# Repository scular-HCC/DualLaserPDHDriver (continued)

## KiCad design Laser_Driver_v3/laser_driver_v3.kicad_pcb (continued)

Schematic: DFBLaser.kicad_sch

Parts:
C66, C67: 100n; C_0805_2012Metric_Pad1.18x1.45mm_HandSolder
C68, C69: 100pF NP0; C_0805_2012Metric_Pad1.18x1.45mm_HandSolder
C70, C71: 10n C0G; C_0805_2012Metric_Pad1.18x1.45mm_HandSolder
C72, C73: 100uF 10V; C_1206_3216Metric_Pad1.33x1.80mm_HandSolder
C74, C75: 100nF X7R; C_0805_2012Metric_Pad1.18x1.45mm_HandSolder
C76, C77: Ci 1n; C_0805_2012Metric_Pad1.18x1.45mm_HandSolder
D22, D23: BAT54 rev prot Vr_max=2V; D_SOD-123
J_BTF1: DFB1550LP #1 Socket; PinSocket_2x07_P2.54mm_Vertical
J_BTF2: DFB1550LP #2 Socket; PinSocket_2x07_P2.54mm_Vertical
L1, L2: 10u (SRF>>20MHz); L_1812_4532Metric_Pad1.30x3.40mm_HandSolder
Q19, Q20: IRLML6344TRPBF; SOT-23
R66, R71: 200k 0.1% scaler_top; R_0805_2012Metric
R67, R72: 1k 0.1% scaler_bot; R_0805_2012Metric
R68, R69, R70, R73, R74, R75, R76, R83, R84, R85, R88, R89, R90, R91: 47R prot; R_0805_2012Metric_Pad1.20x1.40mm_HandSolder
R77, R78: 2k (trim); R_0805_2012Metric_Pad1.20x1.40mm_HandSolder
R79, R80: 10k gate; R_0805_2012Metric_Pad1.20x1.40mm_HandSolder
R81, R82: 0.25R 1W; R_Shunt_Vishay_WSKW0612
R86, R87: 4R7 inrush limit; R_2512_6332Metric
R92, R93: Ri 10k; R_0805_2012Metric_Pad1.20x1.40mm_HandSolder
R94, R95: Rp 1k; R_0805_2012Metric_Pad1.20x1.40mm_HandSolder
R96, R97: Rsum 10k; R_0805_2012Metric_Pad1.20x1.40mm_HandSolder
U22, U23, U24, U25: OPA192IDR; SOT-23-5
U26, U27: ADG419BRM; MSOP-8_3x3mm_P0.65mm

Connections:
+5V: U26.5 (VL), U27.5 (VL); also elsewhere on the board
+5V_LASER: C72.1, C73.1, C74.1, C75.1, R86.1, R87.1; also elsewhere on the board
+15V: U22.5 (V+), U23.5 (V+), U24.4 (V-), U25.4 (V-), U26.4 (V+), U27.4 (V+); also elsewhere on the board
-15V: U22.4 (V-), U23.4 (V-), U24.5 (V+), U25.5 (V+), U26.7 (V-), U27.7 (V-); also elsewhere on the board
AGND: R70.1, R75.2, R85.1, R90.2, U26.3 (GND), U27.3 (GND); also elsewhere on the board
BTF1_LASER: C70.2, D22.1 (K), L1.2, R73.2
BTF1_LASER_K: D22.2 (A), Q19.3 (D), R74.2
BTF2_LASER: C71.2, D23.1 (K), L2.2, R88.2
BTF2_LASER_K: D23.2 (A), Q20.3 (D), R89.2
DITH1_SUM: R67.1, R96.2
DITH2_SUM: R72.1, R97.2
ERR1: R92.1; also elsewhere on the board
ERR2: R93.1; also elsewhere on the board
GND: C72.2, C73.2, C74.2, C75.2, R81.4, R82.4; also elsewhere on the board
LAS1_SENSE_N: R81.3; also elsewhere on the board
LAS1_SENSE_P: C68.1, R81.2, U22.2 (IN-); also elsewhere on the board
LAS2_SENSE_N: R82.3; also elsewhere on the board
LAS2_SENSE_P: C69.1, R82.2, U23.2 (IN-); also elsewhere on the board
LOCK1_EN: U26.6; also elsewhere on the board
LOCK2_EN: U27.6; also elsewhere on the board
MOD1_DRV: C66.1; also elsewhere on the board
MOD2_DRV: C67.1; also elsewhere on the board
NTC1_A: R69.1; also elsewhere on the board
NTC2_A: R84.1; also elsewhere on the board
unnamed: C66.2, R77.1
unnamed: C67.2, R78.1
unnamed: C70.1, R77.2
unnamed: C71.1, R78.2
unnamed: C76.1, R94.1, U26.2
unnamed: C77.1, R95.1, U27.2
unnamed: J_BTF1.10 (CHIP+), R73.1
unnamed: J_BTF1.11 (CHIP-), R74.1
unnamed: J_BTF1.13 (GND), R75.1
unnamed: J_BTF1.2 (NTC_A), R69.2
unnamed: J_BTF1.5 (NTC_GND), R70.2
unnamed: J_BTF1.1 (TEC+), R68.2
unnamed: J_BTF1.14 (TEC-), R76.1
unnamed: J_BTF2.10 (CHIP+), R88.1
unnamed: J_BTF2.11 (CHIP-), R89.1
unnamed: J_BTF2.13 (GND), R90.1
unnamed: J_BTF2.2 (NTC_A), R84.2
unnamed: J_BTF2.5 (NTC_GND), R85.2
unnamed: J_BTF2.1 (TEC+), R83.2
unnamed: J_BTF2.14 (TEC-), R91.1
unnamed: L1.1, R86.2
unnamed: L2.1, R87.2
unnamed: Q19.1 (G), R79.2
unnamed: Q19.2 (S), R81.1
unnamed: Q20.1 (G), R80.2
unnamed: Q20.2 (S), R82.1
unnamed: R66.2, R67.2, U22.3 (IN+)
unnamed: C68.2, R79.1, U22.1 (OUT)
unnamed: R71.2, R72.2, U23.3 (IN+)
unnamed: C69.2, R80.1, U23.1 (OUT)
unnamed: R92.2, R94.2, U24.3 (IN+)
unnamed: C76.2, R96.1, U24.1 (OUT), U26.1
unnamed: R93.2, R95.2, U25.3 (IN+)
unnamed: C77.2, R97.1, U25.1 (OUT), U27.1
TEC1_BTF_N: R76.2; also elsewhere on the board
TEC1_BTF_P: R68.1; also elsewhere on the board
TEC2_BTF_N: R91.2; also elsewhere on the board
TEC2_BTF_P: R83.1; also elsewhere on the board
VOUTA: R66.1; also elsewhere on the board
VOUTB: R71.1; also elsewhere on the board
VREF_MID: U24.2 (IN-), U25.2 (IN-); also elsewhere on the board

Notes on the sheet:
BUTTERFLY CONNECTORS — 2x DFB1550LP | 2x7 2.54mm ZIF sockets
DAC set-point: VOUTB | Dither: DITH2_SUM -> 383k/470nF injection
RF MODULATION INJECTION — BIAS-TEE (per channel) | Copy into DFBLaser.kicad_sch MOD1_DRV (from AD9833 sine, ~0.6 Vpk, Omega ~2 MHz) -> C_ac(DC block) -> R_inj(depth trim) -> C_bt(DC block) -> laser-line node L_bt presents high-Z at Omega (X_L~126R @2MHz) so RF current flows into the laser, not back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
J_BTF2 — Butterfly 2
CAUTION: Verify P10=CHIP+ P11=CHIP- polarity on butterfly connector before first power-on
UNCONFIRMED/NC: P3 P4 P6 P7 P8 P9 P12 — verify MPD pinout
47R series protection resistors on all confirmed pins. Laser Vr_max=2V — NEVER reverse bias.
LASER CHANNEL 2 — U24 / Q18
LASER DRIVER — Two Independent ACC Channels for Thorlabs DFB1550LP | OPA192 Error Amp + IRLML6344 Pass FET + Kelvin Sense
Dither injected at summing node IN+ from laser_control.kicad_sch via DITH1_SUM / DITH2_SUM global labels
Full scale: DAC FS=5V -> scaler /200 -> 25mV at R80 -> OPA192 IN- = 100mA output
J_BTF1 — Butterfly 1
Full scale: DAC FS=5V -> scaler /200 -> 25mV at R79 -> OPA192 IN- = 100mA output
ANALOG PI LOOP FILTER + INTEGRATOR HOLD (per channel) | Copy into new analog sheet / DFBLaser. Inverting PI integrator U830 (OPA192): input Ri=R830=10k from ERR1; feedback = Ci=C830=1n in series with Rp=R831=1k (PI zero). IN+ to VREF_MID. Integrator unity-gain f_i=1/(2*pi*Ri*Ci)~15.9kHz ; PI zero f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
CONFIRMED PINS: P1=TEC+ P2=NTC_A P5=NTC_GND P10=CHIP+ P11=CHIP- P13=GND P14=TEC-
LASER CHANNEL 1 — U23 / Q17
Thorlabs DFB1550LP 1550nm DFB 20mW min Iop=100mA max Vf=3.0V max Vr_max=2V (BAT54 mandatory) Thermistor 10kΩ@25°C
DAC set-point: VOUTA | Dither: DITH1_SUM -> 383k/470nF injection

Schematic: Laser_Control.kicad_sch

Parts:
C80, C82, C84, C85: 100n; C_0805_2012Metric_Pad1.18x1.45mm_HandSolder
C81, C86: 100nF; C_0805_2012Metric_Pad1.18x1.45mm_HandSolder
C83, C87: 10n; C_0805_2012Metric_Pad1.18x1.45mm_HandSolder
NT1: NetTie_3; NetTie-3_THT_Pad1.0mm
U34, U39: AD9833xRM; MSOP-10_3x3mm_P0.5mm
U35, U38: AD9833xRM (ref); MSOP-10_3x3mm_P0.5mm
U36: 74AHCT125; SOIC-14_3.9x8.7mm_P1.27mm
U37: AD5064BRUZ; TSSOP-16_4.4x5mm_P0.65mm

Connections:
3V3: C80.2, C84.2, U34.2 (VDD), U35.2 (VDD), U38.2 (VDD), U39.2 (VDD); also elsewhere on the board
5Vref: U37.7 (V_{REFIN}); also elsewhere on the board
+5V: U36.13 (4~OE), U36.14 (VCC), U37.3 (V_{DD}); also elsewhere on the board
AD5064_CLR: U36.12 (4A); also elsewhere on the board
AGND: C83.2, C87.2, NT1.1, U34.9 (AGND), U35.9 (AGND), U38.9 (AGND), U39.9 (AGND); also elsewhere on the board
CS_3V3: U36.9 (3A); also elsewhere on the board
DDS1_FSYNC: U34.8 (~FSYNC); also elsewhere on the board
DDS2_FSYNC: U39.8 (~FSYNC); also elsewhere on the board
DDS3_FSYNC: U35.8 (~FSYNC); also elsewhere on the board
DDS4_FSYNC: U38.8 (~FSYNC); also elsewhere on the board
DGND: C80.1, C81.1, C82.1, C84.1, C85.1, C86.1, NT1.3, U34.4 (DGND), U35.4 (DGND), U36.1 (1~OE), U36.4 (2~OE), U36.7 (GND), U36.10 (3~OE), U37.1 (~LDAC), U37.6 (POR), U37.12 (GND), U38.4 (DGND), U39.4 (DGND); also elsewhere on the board
GND: NT1.2; also elsewhere on the board
LO1_REF: U35.10 (VOUT); also elsewhere on the board
LO2_REF: U38.10 (VOUT); also elsewhere on the board
MCLK1: U34.5 (MCLK), U35.5 (MCLK); also elsewhere on the board
MCLK2: U38.5 (MCLK), U39.5 (MCLK); also elsewhere on the board
MOD1_DRV: U34.10 (VOUT); also elsewhere on the board
MOD2_DRV: U39.10 (VOUT); also elsewhere on the board
MOSI_3V3: U34.6 (SDATA), U35.6 (SDATA), U36.5 (2A), U38.6 (SDATA), U39.6 (SDATA); also elsewhere on the board
unnamed: C81.2, U34.3 (CAP/2.5V)
unnamed: C82.2, U35.3 (CAP/2.5V)
unnamed: C83.1, U35.1 (COMP)
unnamed: U36.3 (1Y), U37.14 (SCLK)
unnamed: U36.6 (2Y), U37.13 (DIN)
unnamed: U36.8 (3y), U37.2 (~SYNC)
unnamed: U36.11 (4Y), U37.9 (~CLR)
unnamed: C85.2, U38.3 (CAP/2.5V)
unnamed: C87.1, U38.1 (COMP)
unnamed: C86.2, U39.3 (CAP/2.5V)
SCK_3V3: U34.7 (SCLK), U35.7 (SCLK), U36.2 (1A), U38.7 (SCLK), U39.7 (SCLK); also elsewhere on the board
VOUTA: U37.4 (V_{OUT}A); also elsewhere on the board
VOUTB: U37.11 (V_{OUT}B); also elsewhere on the board
VOUTC: U37.5 (V_{OUT}C); also elsewhere on the board
VOUTD: U37.10 (VOUTD); also elsewhere on the board

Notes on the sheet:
DAC: Ch A=Laser1 DC Ch B=Laser2 DC Ch C=TEC1 Ch D=TEC2 | DDS f1=2.000kHz f2=3.100kHz
REFERENCE DDS (per laser) - phase-adjustable demod LO | Each laser has its OWN drive DDS (existing) + reference DDS (this block). Channels stay fully independent - each pair runs its own Omega (Omega_A != Omega_B). PHASE COHERENCE: all four AD9833 share the one 25 MHz Y_DDS via MCLK_REF. Within a l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
AD9833 DDS — Dither generation
V_sense = I_dith * R5 = 0.32mA * 0.25R = 80uV -> LAS_SENSE inferred 1.56mV/scaler confirms ~0.3mA dither
Dither amplitude: 0.32mA peak -> 96MHz FM excursion -> 0.1x HWHM of Q=1e5 ring resonator at 1550nm
f1=2.000kHz: FREQ reg = round(2000 * 2^28 / 25e6) = 0x00056B85
DITHER INJECTION — AC couple + series R sets dither amplitude at laser error amp IN+ summing node
Teensy 3.3V | 74AHCT125 3.3V -> 5V level shift | AD5064 — Quad 16-bit DAC | Ext Vref=5V from LTC6655-5 | VDD=5V from LT3042 U_DAC
f2=3.100kHz: FREQ reg = round(3100 * 2^28 / 25e6) = 0x00086C6C
LASER CONTROL — AD5064 Quad DAC | 74AHCT125 Level Shifter | AD9833 DDS x2 | Dither Injection
Calculation: V_AD9833=0.6Vpk, R_dith=383k, R2=1k -> V_sum=0.6*1k/(383k+1k)=1.56mV
Shared 25MHz crystal Y_DDS. SPI Mode 2 (CPOL=1 CPHA=0). 3.3V — no level shifting needed.

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
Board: 2 copper layers, 198 parts (0 on the bottom side), 187 nets, no tracks yet.

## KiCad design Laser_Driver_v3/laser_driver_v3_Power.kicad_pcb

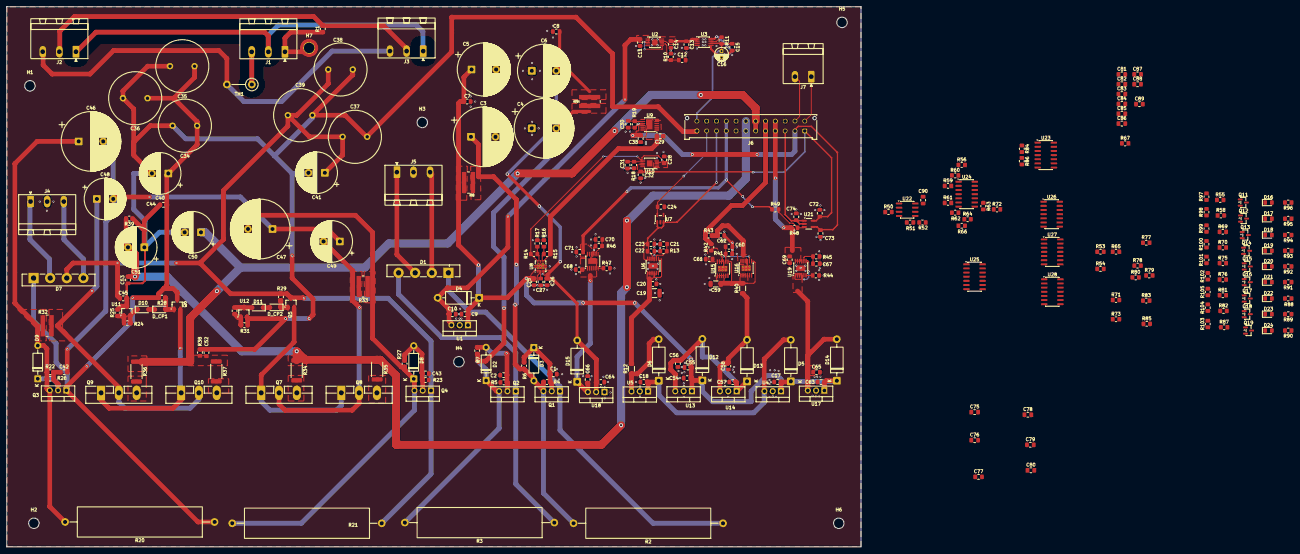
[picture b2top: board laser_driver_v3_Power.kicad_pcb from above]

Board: 2 copper layers, 261.3 x 165.2 mm, 280 parts (0 on the bottom side), 140 nets.

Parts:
C1, C2, C42, C43: 470nF; C_0805_2012Metric_Pad1.18x1.45mm_HandSolder
C3, C4: 2200uF 50V; CP_Radial_D18.0mm_P7.50mm
C5, C6: 1000uF 50V; CP_Radial_D16.0mm_P7.50mm
C7, C8, C44, C45, C52, C53: 2.2 uF; C_0805_2012Metric_Pad1.18x1.45mm_HandSolder
C9, C10, C14, C17, C18, C27, C55, C58, C72, C73, C74, C75, C76, C77, C78, C79, C80, C90: 100nF; C_0805_2012Metric_Pad1.18x1.45mm_HandSolder
C11, C13, C54, C56: 4.7uF; C_0805_2012Metric_Pad1.18x1.45mm_HandSolder
C12, C21, C30, C31, C60, C67, C70: 4.7uF X7R; C_0805_2012Metric_Pad1.18x1.45mm_HandSolder
C15, C25, C26, C28, C29, C32, C33, C61, C62, C65, C66, C68, C71: 10uF; C_0805_2012Metric_Pad1.18x1.45mm_HandSolder
C16: 10uF 16V Polymer; CP_Radial_D4.0mm_P2.00mm
C19: 47uF RC; C_1210_3225Metric_Pad1.33x2.70mm_HandSolder
C20: 4.7uF RC; C_0805_2012Metric_Pad1.18x1.45mm_HandSolder
C22, C69: 10uF X5R or X7R; C_0805_2012Metric_Pad1.18x1.45mm_HandSolder
C23, C24: 1uF; C_0805_2012Metric_Pad1.18x1.45mm_HandSolder
C34, C35, C36, C37, C38, C39: 3300uF (UPW1E332MHD); C_Radial_D16.0mm_H25.0mm_P7.50mm
C40, C41, C48, C49: 1000uF 25V; CP_Radial_D12.5mm_P5.00mm
C46, C47: 2200uF 35V; CP_Radial_D18.0mm_P7.50mm
C50: 1000 uF C_out+; CP_Radial_D12.5mm_P5.00mm
C51: 1000 uF C_out-; CP_Radial_D12.5mm_P5.00mm
C57, C63, C64: 0.33uF; C_0805_2012Metric_Pad1.18x1.45mm_HandSolder
C59: 100uF; C_1206_3216Metric_Pad1.33x1.80mm_HandSolder
C81, C82, C83, C84, C85, C86, C87, C88, C89: 10nF; C_0805_2012Metric_Pad1.18x1.45mm_HandSolder
D1: GBU4M; Diode_Bridge_Vishay_GBU
D2, D3, D8, D9: 1N4742A; D_DO-41_SOD81_P10.16mm_Horizontal
D4, D5, D6, D12, D13, D14, D15: 1N4007; D_DO-15_P12.70mm_Horizontal
D7: GBU1506; Diode_Bridge_Vishay_GBU
D10, D11: 1N4148W; D_SOD-123
D16: +15V_OK; LED_0805_2012Metric_Pad1.15x1.40mm_HandSolder
D17: -15V_OK; LED_0805_2012Metric_Pad1.15x1.40mm_HandSolder
D18: +5V_OK; LED_0805_2012Metric_Pad1.15x1.40mm_HandSolder
D19: -5V_OK; LED_0805_2012Metric_Pad1.15x1.40mm_HandSolder
D20: +6V_OK; LED_0805_2012Metric_Pad1.15x1.40mm_HandSolder
D21: -6V_OK; LED_0805_2012Metric_Pad1.15x1.40mm_HandSolder
D22: +5VLaser_OK; LED_0805_2012Metric_Pad1.15x1.40mm_HandSolder
D23: 3V3_OK; LED_0805_2012Metric_Pad1.15x1.40mm_HandSolder
D24: 1V8_OK; LED_0805_2012Metric_Pad1.15x1.40mm_HandSolder
D_CP1, D_CP2: 1N4148; D_SOD-123
H1, H2, H3, H4, H5, H6: MountingHole; MountingHole_3.2mm_M3
H7: GND; MountingHole_3.2mm_M3_DIN965_Pad_TopBottom
J1, J2, J3, J4, J5: Screw_Terminal_01x03; PhoenixContact_MSTBA_2,5_3-G-5,08_1x03_P5.08mm_Horizontal
J6: Conn_02x12_Counter_Clockwise; Molex_Micro-Fit_3.0_43045-2412_2x12_P3.00mm_Vertical
J7: Conn_01x02_Pin; PhoenixContact_MSTBA_2,5_2-G_1x02_P5.00mm_Horizontal
Q1, Q3: IRF540NPBF; TO-220-3_Vertical
Q2, Q4: IRF9540NPBF; TO-220-3_Vertical
Q5: MMBT2907; SOT-23_Handsoldering
Q6: MMBT2222; SOT-23_Handsoldering
Q7, Q8: Q_PNP_MJL21193; TO-264-3_Vertical
Q9, Q10: Q_NPN MJL21194; TO-264-3_Vertical
Q11, Q12, Q13, Q14, Q15, Q16, Q17, Q18, Q19: MMBT3904; SOT-23
R1, R11, R16, R17, R51: 1k; R_0805_2012Metric_Pad1.20x1.40mm_HandSolder
R2, R3: 15; R_Axial_Power_L38.0mm_W9.0mm_P45.72mm
R4, R5, R22, R23: 1M; R_0805_2012Metric_Pad1.20x1.40mm_HandSolder
R6, R7, R26, R27: 100k; R_0805_2012Metric_Pad1.20x1.40mm_HandSolder
R8: 4.75 2W; RESC3263X80N
R9: 4.75, 2+W; RESC3263X80N
R10: 54.9k 0.1%; R_0805_2012Metric_Pad1.20x1.40mm_HandSolder
R12: 4.7R; R_1206_3216Metric_Pad1.30x1.75mm_HandSolder
R13: 33k 0.1%; R_0805_2012Metric_Pad1.20x1.40mm_HandSolder
R14, R15: 12.7k 0.1%; R_0805_2012Metric_Pad1.20x1.40mm_HandSolder
R18, R19: 143k 0.1%; R_0805_2012Metric_Pad1.20x1.40mm_HandSolder
R20, R21: 15R; R_Axial_Power_L38.0mm_W9.0mm_P45.72mm
R24, R31: 15k; R_0805_2012Metric_Pad1.20x1.40mm_HandSolder
R25, R30: 60.4k; R_0805_2012Metric_Pad1.20x1.40mm_HandSolder
R28, R29: 1.5k Bias; R_0805_2012Metric_Pad1.20x1.40mm_HandSolder
R32, R33: 4.75R 2W; RESC3263X80N
R34, R35, R36, R37: 0.1R; R_2512_6332Metric_Pad1.40x3.35mm_HandSolder
R38, R39: 1k bleed resistor; R_0805_2012Metric_Pad1.20x1.40mm_HandSolder
R40: 1R RC; R_1206_3216Metric_Pad1.30x1.75mm_HandSolder
R41: 49.9k 0.1%; R_0805_2012Metric_Pad1.20x1.40mm_HandSolder
R42, R43: 20m PCB Trace; R_0805_2012Metric_Pad1.20x1.40mm_HandSolder
R44, R47: 16k; R_0805_2012Metric_Pad1.20x1.40mm_HandSolder
R45, R46: 50k 0.1%; R_0805_2012Metric_Pad1.20x1.40mm_HandSolder
R48, R49, R54, R55, R58, R60, R62, R63, R67, R69, R70, R73, R75, R76, R79, R80, R81, R82, R84, R85, R86, R87: 10k; R_0805_2012Metric_Pad1.20x1.40mm_HandSolder
R50: 29.4k; R_0805_2012Metric_Pad1.20x1.40mm_HandSolder
R52: 9.53k; R_0805_2012Metric_Pad1.20x1.40mm_HandSolder
R53: 110k; R_0805_2012Metric_Pad1.20x1.40mm_HandSolder
R56, R66, R72: 100; R_0805_2012Metric_Pad1.20x1.40mm_HandSolder
R59: 120k; R_0805_2012Metric_Pad1.20x1.40mm_HandSolder
R61: 40.2k; R_0805_2012Metric_Pad1.20x1.40mm_HandSolder
R64: 47.5k; R_0805_2012Metric_Pad1.20x1.40mm_HandSolder
R65, R77: 30.1k; R_0805_2012Metric_Pad1.20x1.40mm_HandSolder
R71: 38.3k; R_0805_2012Metric_Pad1.20x1.40mm_HandSolder
R78: 16.5k; R_0805_2012Metric_Pad1.20x1.40mm_HandSolder
R83: 4.42k; R_0805_2012Metric_Pad1.20x1.40mm_HandSolder
R88, R89, R90, R91, R92, R93, R94, R95, R96: 1.3k; R_0805_2012Metric_Pad1.20x1.40mm_HandSolder
R97, R98, R99, R100, R101, R102, R103, R104, R105: 4.7k; R_0805_2012Metric_Pad1.20x1.40mm_HandSolder
TH1: Ametherm SL22 10005; R_Axial_DIN0411_L9.9mm_D3.6mm_P7.62mm_Vertical
U1, U14, U17: MC7808CTG; TO-220-3_Vertical
U2: LT3042EMSE +5.5V; MSOP-10-1EP_3x3mm_P0.5mm_EP1.68x1.88mm
U3: LTC6655BHMS8-5#PBF; MSOP-8_3x3mm_P0.65mm
U4, U13: MC7812CTG; TO-220-3_Vertical
U5: MC7805CTG; TO-220-3_Vertical
U6: LT3045EMSE 3.3V; MSOP-12-1EP_3x4.039mm_P0.65mm_EP1.651x2.845mm
U7: LP5907MFX-1.8; SOT-23-5
U8: TPS7A3901DSCR; Texas_DSC0010J_ThermalVias
U9: LT3094EMSE -14.3V; MSOP-12-1EP_3x4.039mm_P0.65mm_EP1.651x2.845mm
U10: LT3042EMSE +14.3V; MSOP-10-1EP_3x3mm_P0.5mm_EP1.68x1.88mm
U11, U12: LM4051AIM3-ADJ/NOPB; SOT-23_Handsoldering
U15, U16: LT3045EMSE 5V; MSOP-12-1EP_3x4.039mm_P0.65mm_EP1.651x2.845mm_ThermalVias
U18: LM7905_TO220; TO-220-3_Vertical
U19: LT3045EMSE 5V; MSOP-12-1EP_3x4.039mm_P0.65mm_EP1.651x2.845mm
U20: LT3094EMSE -5V; MSOP-12-1EP_3x4.039mm_P0.65mm_EP1.651x2.845mm
U21: OPA192IDBVR; SOT-23-5_HandSoldering
U22: MCP6002-xMC; SOIC-8_3.9x4.9mm_P1.27mm
U23, U25, U26, U27, U28: LM339; SOIC-14_3.9x8.7mm_P1.27mm
U24: MCP6004; SOIC-14_3.9x8.7mm_P1.27mm

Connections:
0Vac: J1.2, J2.1, J3.1
1V8: C24.2, C81.2, J6.11, R83.1, U7.5 (OUT), U28.9 (+), U28.11 (+)
3V3: C22.1, C23.2, J6.10, R78.1, U6.10 (OUTS), U6.11 (OUT), U6.12 (OUT), U7.1 (IN), U7.3 (EN)
5Vref: C15.1, C16.1, J6.24, R11.2, R50.1, U3.6 (VOUTS)
120Vac: J1.3, TH1.1
+5V: C69.1, C75.1, C76.1, C77.1, C78.1, C79.1, C80.1, C90.1, J6.4, J6.16, R48.2, R65.1, R84.1, R88.1, R89.1, R90.1, R91.1, R92.1, R93.1, R94.1, R95.1, R96.1, R97.2, R98.2, R99.2, R100.2, R101.2, R102.2, R103.2, R104.2, R105.2, U19.10 (OUTS), U19.11 (OUT), U19.12 (OUT), U22.8 (V+), U23.3 (V+), U24.4 (V+), U25.3 (V+), U26.3 (V+), U27.3 (V+), U28.3 (V+)
+5V_LASER: J6.5, J6.17, R42.2, R43.2, R77.1
+6V_TEC: C50.1, C52.1, J6.6, J6.18, R36.1, R37.1, R38.1, R71.1
+9Vac: D7.4, J4.3
+15V: C32.1, C72.1, J6.1, R53.1, U10.9 (OUTS), U10.10 (OUT), U21.5 (V+)
+22V: C5.1, C7.1, C9.1, C17.1, C25.1, C54.1, C55.1, C63.1, D4.1 (K), D5.1 (K), D12.1 (K), D14.1 (K), R8.2, U1.1 (VI), U4.1 (VI), U8.1 (INP), U8.2 (EN), U13.1 (VI), U17.1 (VI)
-5V: C71.2, J6.9, J6.21, R49.1, R61.1, U20.10 (OUTS), U20.11 (OUT), U20.12 (OUT)
-6V_TEC: C51.2, C53.2, J6.7, J6.19, R34.1, R35.1, R39.2, R64.1
-9Vac: D7.2, J4.1
-15V: C33.2, C73.1, J6.2, R59.1, U9.10 (OUTS), U9.11 (OUT), U9.12 (OUT), U21.4 (V-)
-22V: C6.2, C8.2, C26.1, C64.2, D15.2 (A), R9.2, U8.5 (INN), U18.2 (VI)
/+-6V TEC/TEC_RAW+: C34.1, C35.1, C36.1, C40.1, C44.1, D7.1 (+), Q3.1 (D), Q6.3 (C), R20.1, R28.2
/+-6V TEC/TEC_RAW-: C37.1, C38.1, C39.1, C41.1, C45.1, D7.3 (-), Q4.1 (D), Q5.3 (C), R21.1, R29.1
/Mains to +-18V/+22VNF: C3.1, D3.2 (A), Q1.3 (S), R2.2, R4.2, R6.1, R8.1
/Mains to +-18V/-22VNF: C4.2, D2.1 (K), Q2.3 (S), R3.2, R7.1, R9.1
/Mains to +-18V/RAW22+: D1.1 (+), Q1.1 (D), R2.1
/Mains to +-18V/RAW22-: D1.4 (-), Q2.1 (D), R3.1
/VoltageMonitor/VHI: R50.2, R51.1, U22.3 (+)
/VoltageMonitor/VLO: R51.2, R52.1, U22.5 (+)
DGND: C34.2, C35.2, C36.2, C37.2, C38.2, C39.2, C40.2, C41.2, C44.2, C45.2, C50.2, C51.1, C52.2, C53.1, J6.12, R25.1, R31.2, R38.2, R39.1, U11.3 (A), U12.2 (K)
Earth: H7.1 (1_1), J1.1, R1.1
GND: C1.2, C2.2, C3.2, C4.1, C5.2, C6.1, C7.2, C8.1, C9.2, C10.2, C11.2, C12.2, C13.2, C14.2, C15.2, C16.2, C17.2, C18.2, C19.2, C20.2, C21.2, C22.2, C23.1, C24.1, C25.2, C26.2, C27.1, C28.2, C29.2, C30.2, C31.2, C32.2, C33.1, C43.2, C54.2, C55.2, C56.2, C57.2, C58.2, C59.2, C60.2, C61.2, C62.2, C63.2, C64.1, C65.2, C66.1, C67.2, C68.2, C69.2, C70.2, C71.1, C72.2, C73.2, C74.2, C75.2, C76.2, C77.2, C78.2, C79.2, C80.2, C82.2, C83.2, C84.2, C85.2, C86.2, C87.2, C88.2, C89.2, C90.2, J4.2, J6.8, J6.15, J6.20, J6.22, J6.23, Q11.2 (E), Q12.2 (E), Q13.2 (E), Q14.2 (E), Q15.2 (E), Q16.2 (E), Q17.2 (E), Q18.2 (E), Q19.2 (E), R5.2, R10.2, R13.2, R16.2, R17.2, R18.2, R19.2, R23.2, R41.2, R44.2, R45.2, R46.2, R47.2, R52.2, R54.2, R67.2, R73.2, R79.2, R80.2, R85.2, R86.2, U1.2 (GND), U2.5 (ILIM), U2.8 (GND), U2.11 (GND), U3.3 (GND), U3.4 (GND), U3.5 (GND), U3.8 (GND), U4.2 (GND), U5.2 (GND), U6.6 (ILIM), U6.9 (GND), U6.13 (GND), U7.2 (GND), U8.4 (GND), U8.11 (GND), U9.6 (ILIM), U9.9 (GND), U10.5 (ILIM), U10.8 (GND), U10.11 (GND), U13.2 (GND), U14.2 (GND), U15.6 (ILIM), U15.9 (GND), U15.13 (EXP), U16.6 (ILIM), U16.9 (GND), U16.13 (EXP), U17.2 (GND), U18.1 (GND), U19.9 (GND), U19.13 (GND), U20.9 (GND), U22.4 (V-), U23.12 (V-), U24.3 (+), U24.5 (+), U24.10 (+), U24.11 (V-), U25.12 (V-), U26.12 (V-), U27.12 (V-), U28.8 (-), U28.10 (-), U28.12 (V-)
unnamed: C42.2, C46.2, C47.1, C48.2, C49.1
unnamed: C2.1, D2.2 (A), Q2.2 (G), R5.1, R7.2
unnamed: C1.1, D3.1 (K), Q1.2 (G), R4.1, R6.2
unnamed: C10.1, C11.1, D4.2 (A), U1.3 (VO), U2.1 (IN), U2.2 (IN), U2.3 (EN/UV), U2.6 (PGFB)
unnamed: C18.1, D5.2 (A), D6.1 (K), U4.3 (VO), U5.1 (VI)
unnamed: D6.2 (A), R12.1, U5.3 (VO)
unnamed: C43.1, D8.2 (A), Q4.2 (G), R23.1, R27.2
unnamed: C47.2, D8.1 (K), Q4.3 (S), R21.2, R27.1, R33.1
unnamed: C46.1, D9.2 (A), Q3.3 (S), R20.2, R22.2, R26.1, R32.1
unnamed: C42.1, D9.1 (K), Q3.2 (G), R22.1, R26.2
unnamed: D10.2 (A), D_CP1.1 (K)
unnamed: D10.1 (K), R24.2, U11.2 (K)
unnamed: D11.2 (A), R30.1, U12.3 (A)
unnamed: D11.1 (K), D_CP2.2 (A)
unnamed: C56.1, C57.1, D12.2 (A), D13.1 (K), U13.3 (VO), U14.1 (VI)
unnamed: C58.1, D13.2 (A), R40.1, U14.3 (VO)
unnamed: C65.1, D14.2 (A), U17.3 (VO), U19.1 (IN), U19.2 (IN), U19.3 (IN), U19.4 (EN/UV), U19.7 (PGFB)
unnamed: C66.2, C68.1, D15.1 (K), U18.3 (VO), U20.1 (IN), U20.2 (IN), U20.3 (EN/UV), U20.5 (PGFB), U20.13 (IN)
unnamed: D16.2 (A), R96.2
unnamed: D16.1 (K), Q11.3 (C)
unnamed: D17.2 (A), R95.2
unnamed: D17.1 (K), Q12.3 (C)
unnamed: D18.2 (A), R94.2
unnamed: D18.1 (K), Q13.3 (C)
unnamed: D19.2 (A), R93.2
unnamed: D19.1 (K), Q14.3 (C)
unnamed: D20.2 (A), R92.2
unnamed: D20.1 (K), Q15.3 (C)
unnamed: D21.2 (A), R91.2
unnamed: D21.1 (K), Q16.3 (C)
unnamed: D22.2 (A), R88.2
unnamed: D22.1 (K), Q17.3 (C)
unnamed: D23.2 (A), R89.2
unnamed: D23.1 (K), Q18.3 (C)
unnamed: D24.2 (A), R90.2
unnamed: D24.1 (K), Q19.3 (C)
unnamed: D_CP1.2 (A), Q6.1 (B), R28.1
unnamed: D_CP2.1 (K), Q5.1 (B), R29.2
unnamed: J2.2, J3.2, R1.2
unnamed: J2.3, J3.3, TH1.2
unnamed: D1.3, J5.1
unnamed: D1.2, J5.3
unnamed: J6.13, J7.1
unnamed: J6.14, J7.2
unnamed: Q5.2 (E), Q7.1 (B), Q8.1 (B)
unnamed: C49.2, Q7.2 (C), Q8.2 (C), R33.2
unnamed: Q7.3 (E), R34.2
unnamed: Q8.3 (E), R35.2
unnamed: Q9.3 (E), R36.2
unnamed: Q6.2 (E), Q9.1 (B), Q10.1 (B)
unnamed: C48.1, Q9.2 (C), Q10.2 (C), R32.2
unnamed: Q10.3 (E), R37.2
unnamed: Q11.1 (B), R55.2
unnamed: Q12.1 (B), R58.2
unnamed: Q13.1 (B), R69.2
unnamed: Q14.1 (B), R70.2
unnamed: Q15.1 (B), R75.2
unnamed: Q16.1 (B), R76.2
unnamed: Q17.1 (B), R81.2
unnamed: Q18.1 (B), R82.2
unnamed: Q19.1 (B), R87.2
unnamed: R55.1, R97.1, U23.1, U23.2
unnamed: R56.1, R60.2, U24.1
unnamed: R58.1, R98.1, U23.13, U23.14
unnamed: R62.2, R66.1, U24.7
unnamed: R63.2, R72.1, U24.8
unnamed: R69.1, R99.1, U25.1, U25.2
unnamed: R70.1, R100.1, U25.13, U25.14
unnamed: R75.1, R101.1, U26.1, U26.2
unnamed: R76.1, R102.1, U26.13, U26.14
unnamed: R87.1, R103.1, U28.1, U28.2
unnamed: R82.1, R104.1, U27.13, U27.14
unnamed: R81.1, R105.1, U27.1, U27.2
unnamed: C13.1, C14.1, U2.9 (OUTS), U2.10 (OUT), U3.1 (SHDN), U3.2 (VIN)
unnamed: C12.1, R10.1, U2.7 (SET)
unnamed: R11.1, U3.7 (VOUTF)
unnamed: C19.1, C20.1, R12.2, U6.1 (IN), U6.2 (IN), U6.3 (IN), U6.4 (EN/UV), U6.7 (PGFB)
unnamed: C21.1, R13.1, U6.8 (SET)
unnamed: R15.2, R16.1, U8.7 (FBN)
unnamed: R14.2, R17.1, U8.9 (FBP)
unnamed: C27.2, U8.3 (NR/SS)
unnamed: C29.1, R15.1, U8.6 (OUTN), U9.1 (IN), U9.2 (IN), U9.3 (EN/UV), U9.5 (PGFB), U9.13 (IN)
unnamed: C30.1, R19.1, U9.8 (SET)
unnamed: C28.1, R14.1, U8.10 (OUTP), U10.1 (IN), U10.2 (IN), U10.3 (EN/UV), U10.6 (PGFB)
unnamed: C31.1, R18.1, U10.7 (SET)
unnamed: R24.1, R25.2, U11.1 (FB)
unnamed: R30.2, R31.1, U12.1 (FB)
unnamed: C59.1, R40.2, U15.1 (IN), U15.2 (IN), U15.3 (IN), U15.4 (EN/UV), U15.7 (PGFB), U16.1 (IN), U16.2 (IN), U16.3 (IN), U16.4 (EN/UV), U16.7 (PGFB)
unnamed: C61.1, R42.1, U15.10 (OUTS), U15.11 (OUT), U15.12 (OUT)
unnamed: C60.1, R41.1, U15.8 (SET), U16.8 (SET)
unnamed: C62.1, R43.1, U16.10 (OUTS), U16.11 (OUT), U16.12 (OUT)
unnamed: R44.1, U19.6 (ILIM)
unnamed: C67.1, R45.1, U19.8 (SET)
unnamed: R47.1, U20.6 (ILIM)
unnamed: C70.1, R46.1, U20.8 (SET)
unnamed: R48.1, R49.2, U21.3 (IN+)
unnamed: C84.1, R53.2, R54.1, U23.4 (-), U23.7 (+)
unnamed: C85.1, R56.2, U23.9 (+), U23.10 (-)
unnamed: R59.2, R60.1, U24.2 (-)
unnamed: R61.2, R62.1, U24.6 (-)
unnamed: R63.1, R64.2, U24.9 (-)
unnamed: R84.2, R86.1, U24.12 (+)
unnamed: U24.13 (-), U24.14
unnamed: C86.1, R65.2, R67.1, U25.4 (-), U25.7 (+)
unnamed: C87.1, R66.2, U25.9 (+), U25.10 (-)
unnamed: C88.1, R71.2, R73.1, U26.4 (-), U26.7 (+)
unnamed: C89.1, R72.2, U26.9 (+), U26.10 (-)
unnamed: C83.1, R77.2, R79.1, U27.4 (-), U27.7 (+)
unnamed: C82.1, R78.2, R80.1, U27.9 (+), U27.10 (-)
unnamed: C81.1, R83.2, R85.1, U28.4 (-), U28.7 (+)
VHI_Buf: U22.1, U22.2 (-), U23.5 (+), U23.11 (+), U25.5 (+), U25.11 (+), U26.5 (+), U26.11 (+), U27.5 (+), U27.11 (+), U28.5 (+)
VLO_Buf: U22.6 (-), U22.7, U23.6 (-), U23.8 (-), U25.6 (-), U25.8 (-), U26.6 (-), U26.8 (-), U27.6 (-), U27.8 (-), U28.6 (-)
VREF_MID: C74.1, J6.3, U21.1 (OUT), U21.2 (IN-)
